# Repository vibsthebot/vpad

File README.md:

# vpad - a 50-key split keyboard

vpad is a wired, split, and ortholinear mechanical keyboard. both sides of the keyboard use the same board, and are connected using a ten wire cable. each half uses a 5x5 key matrix using choc v1 switches. 

## Features
well its just a simple keyboard, but its ortholinear, split, and choc!

## Firmware Overview
- Layer 0 - QWERTY (Default)
- Layer 1 - Numbers & Symbols
- Layer 2 - Function Keys

### Schematic

### PCB

### 3D Model

### BOM
| Qty	| Item	| Individual Price	| Total Price	|
| - | - | - | - |
| 1	|PCB + stencil	|$15.20	|$15.20	|
|50|	SOD123 Diode	| $0.02	| $1.15	| BAV21WTPMSCT-ND |
|1x80|	M3x4 heatset insert	|	$5.99	| https://www.amazon.com/Threaded-Inserts-Printing-Embedment-Automotive/dp/B0DJS5HWBY/ |
|50|	Choc v1|	$0.60	 |$30.00	|
|1x100|	M3x6 screws|$5.99	|https://www.amazon.com/Socket-Screws-Bolts-Thread-100pcs/dp/B07CMRQ3TB/|
|-|-|$58.33	|

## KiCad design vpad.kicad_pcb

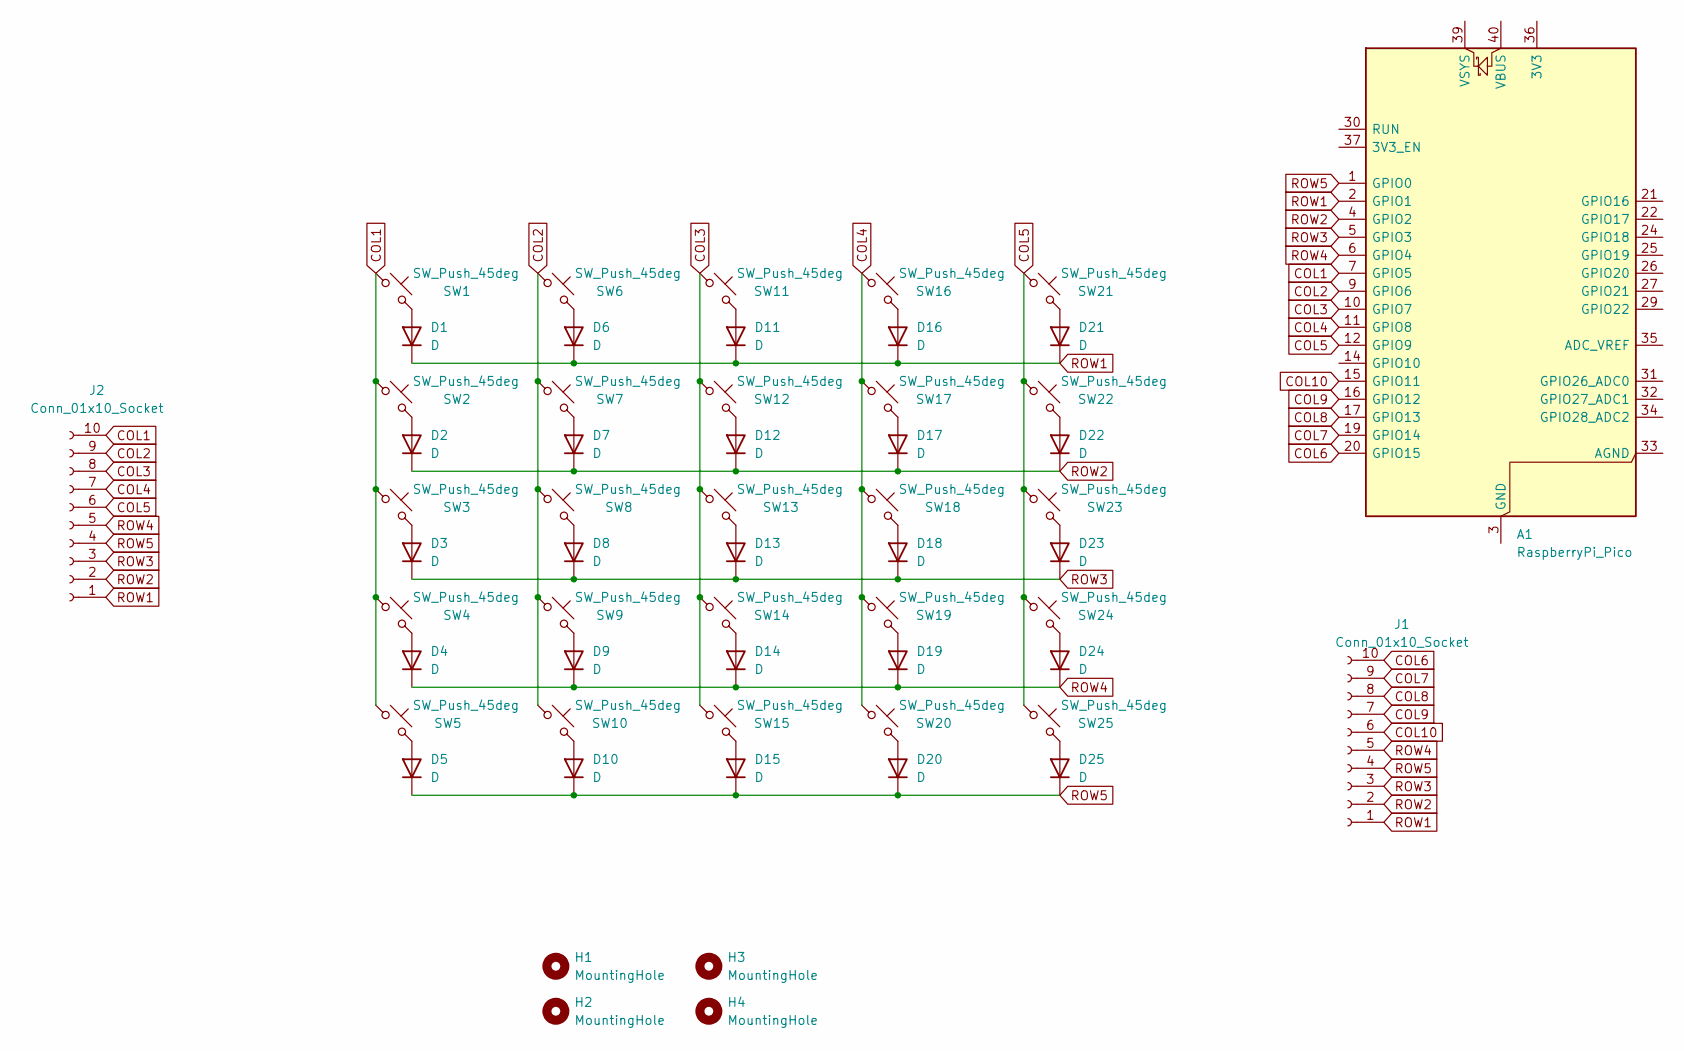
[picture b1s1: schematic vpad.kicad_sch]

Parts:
A1: RaspberryPi_Pico; RaspberryPi_Pico_Common_THT
D1, D2, D3, D4, D5, D6, D7, D8, D9, D10, D11, D12, D13, D14, D15, D16, D17, D18, D19, D20, D21, D22, D23, D24, D25: D; Diode_SOD-123
H1, H2, H3, H4: MountingHole; MountingHole_3.2mm_M3
J1, J2: Conn_01x10_Socket; PinSocket_1x10_P2.54mm_Vertical
SW1, SW2, SW3, SW4, SW5, SW6, SW7, SW8, SW9, SW10, SW11, SW12, SW13, SW14, SW15, SW16, SW17, SW18, SW19, SW20, SW21, SW22, SW23, SW24, SW25: SW_Push_45deg; Choc_V1_1.00u

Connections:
COL1: A1.7 (GPIO5), J2.10, SW1.1, SW2.1, SW3.1, SW4.1, SW5.1
COL2: A1.9 (GPIO6), J2.9, SW6.1, SW7.1, SW8.1, SW9.1, SW10.1
COL3: A1.10 (GPIO7), J2.8, SW11.1, SW12.1, SW13.1, SW14.1, SW15.1
COL4: A1.11 (GPIO8), J2.7, SW16.1, SW17.1, SW18.1, SW19.1, SW20.1
COL5: A1.12 (GPIO9), J2.6, SW21.1, SW22.1, SW23.1, SW24.1, SW25.1
COL6: A1.20 (GPIO15), J1.10
COL7: A1.19 (GPIO14), J1.9
COL8: A1.17 (GPIO13), J1.8
COL9: A1.16 (GPIO12), J1.7
COL10: A1.15 (GPIO11), J1.6
unnamed: A1.3 (GND), A1.8 (GND), A1.13 (GND), A1.18 (GND), A1.23 (GND), A1.28 (GND), A1.38 (GND)
unnamed: D1.2 (A), SW1.2
unnamed: D2.2 (A), SW2.2
unnamed: D3.2 (A), SW3.2
unnamed: D4.2 (A), SW4.2
unnamed: D5.2 (A), SW5.2
unnamed: D6.2 (A), SW6.2
unnamed: D7.2 (A), SW7.2
unnamed: D8.2 (A), SW8.2
unnamed: D9.2 (A), SW9.2
unnamed: D10.2 (A), SW10.2
unnamed: D11.2 (A), SW11.2
unnamed: D12.2 (A), SW12.2
unnamed: D13.2 (A), SW13.2
unnamed: D14.2 (A), SW14.2
unnamed: D15.2 (A), SW15.2
unnamed: D16.2 (A), SW16.2
unnamed: D17.2 (A), SW17.2
unnamed: D18.2 (A), SW18.2
unnamed: D19.2 (A), SW19.2
unnamed: D20.2 (A), SW20.2
unnamed: D21.2 (A), SW21.2
unnamed: D22.2 (A), SW22.2
unnamed: D23.2 (A), SW23.2
unnamed: D24.2 (A), SW24.2
unnamed: D25.2 (A), SW25.2
ROW1: A1.2 (GPIO1), D1.1 (K), D6.1 (K), D11.1 (K), D16.1 (K), D21.1 (K), J1.1, J2.1
ROW2: A1.4 (GPIO2), D2.1 (K), D7.1 (K), D12.1 (K), D17.1 (K), D22.1 (K), J1.2, J2.2
ROW3: A1.5 (GPIO3), D3.1 (K), D8.1 (K), D13.1 (K), D18.1 (K), D23.1 (K), J1.3, J2.3
ROW4: A1.6 (GPIO4), D4.1 (K), D9.1 (K), D14.1 (K), D19.1 (K), D24.1 (K), J1.5, J2.5
ROW5: A1.1 (GPIO0), D5.1 (K), D10.1 (K), D15.1 (K), D20.1 (K), D25.1 (K), J1.4, J2.4

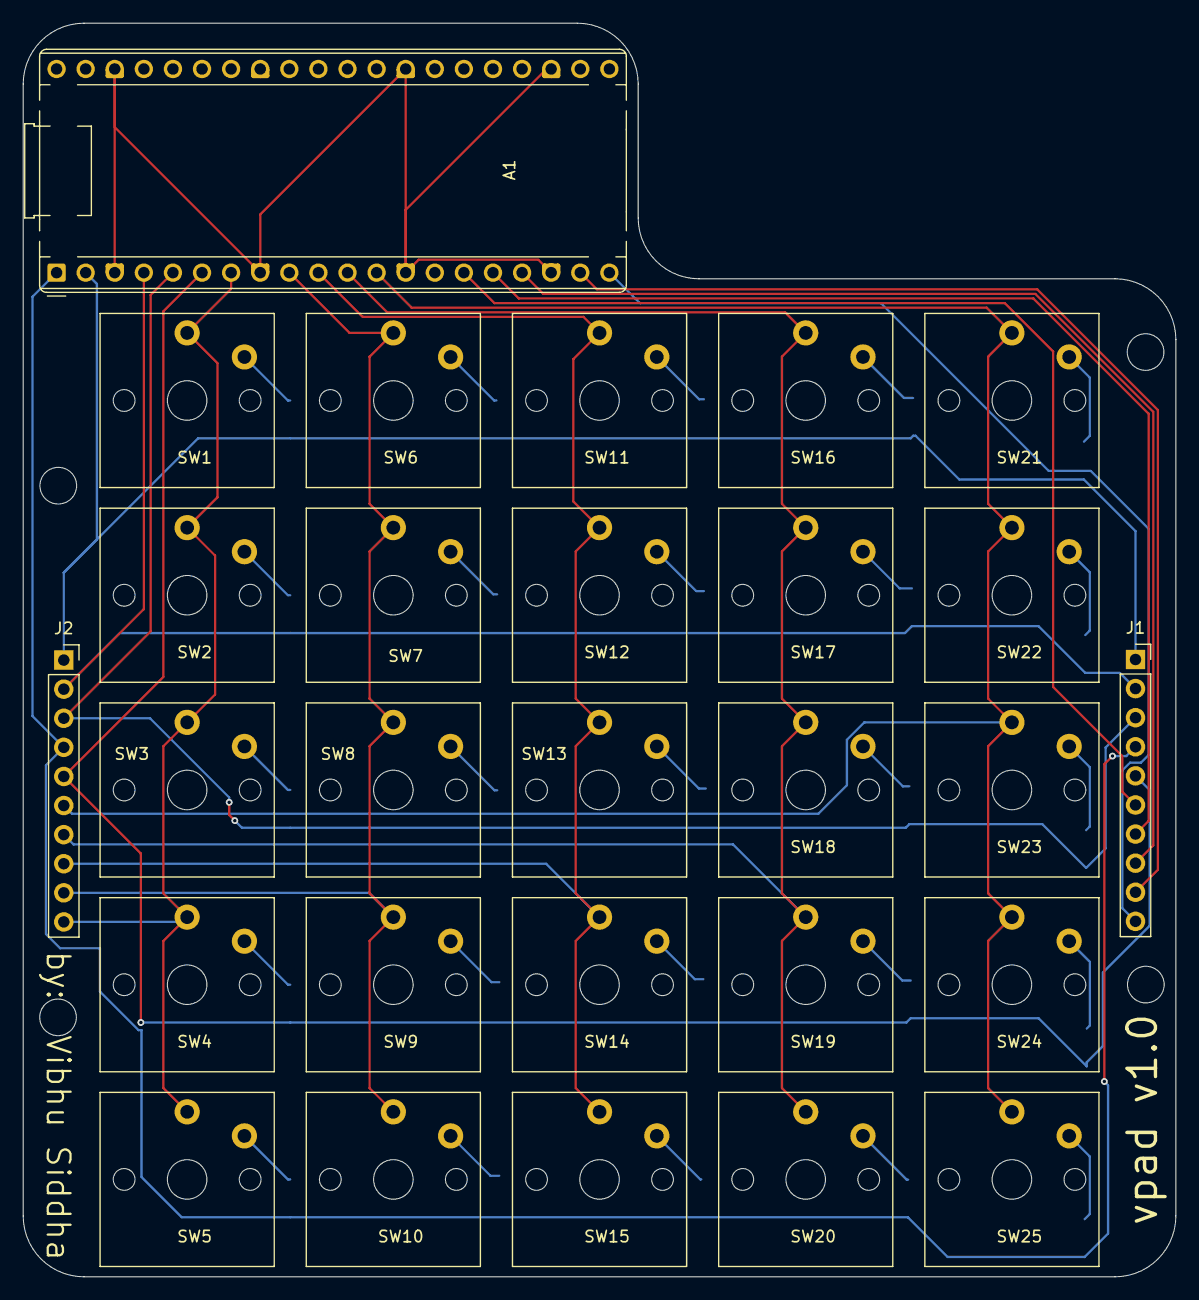
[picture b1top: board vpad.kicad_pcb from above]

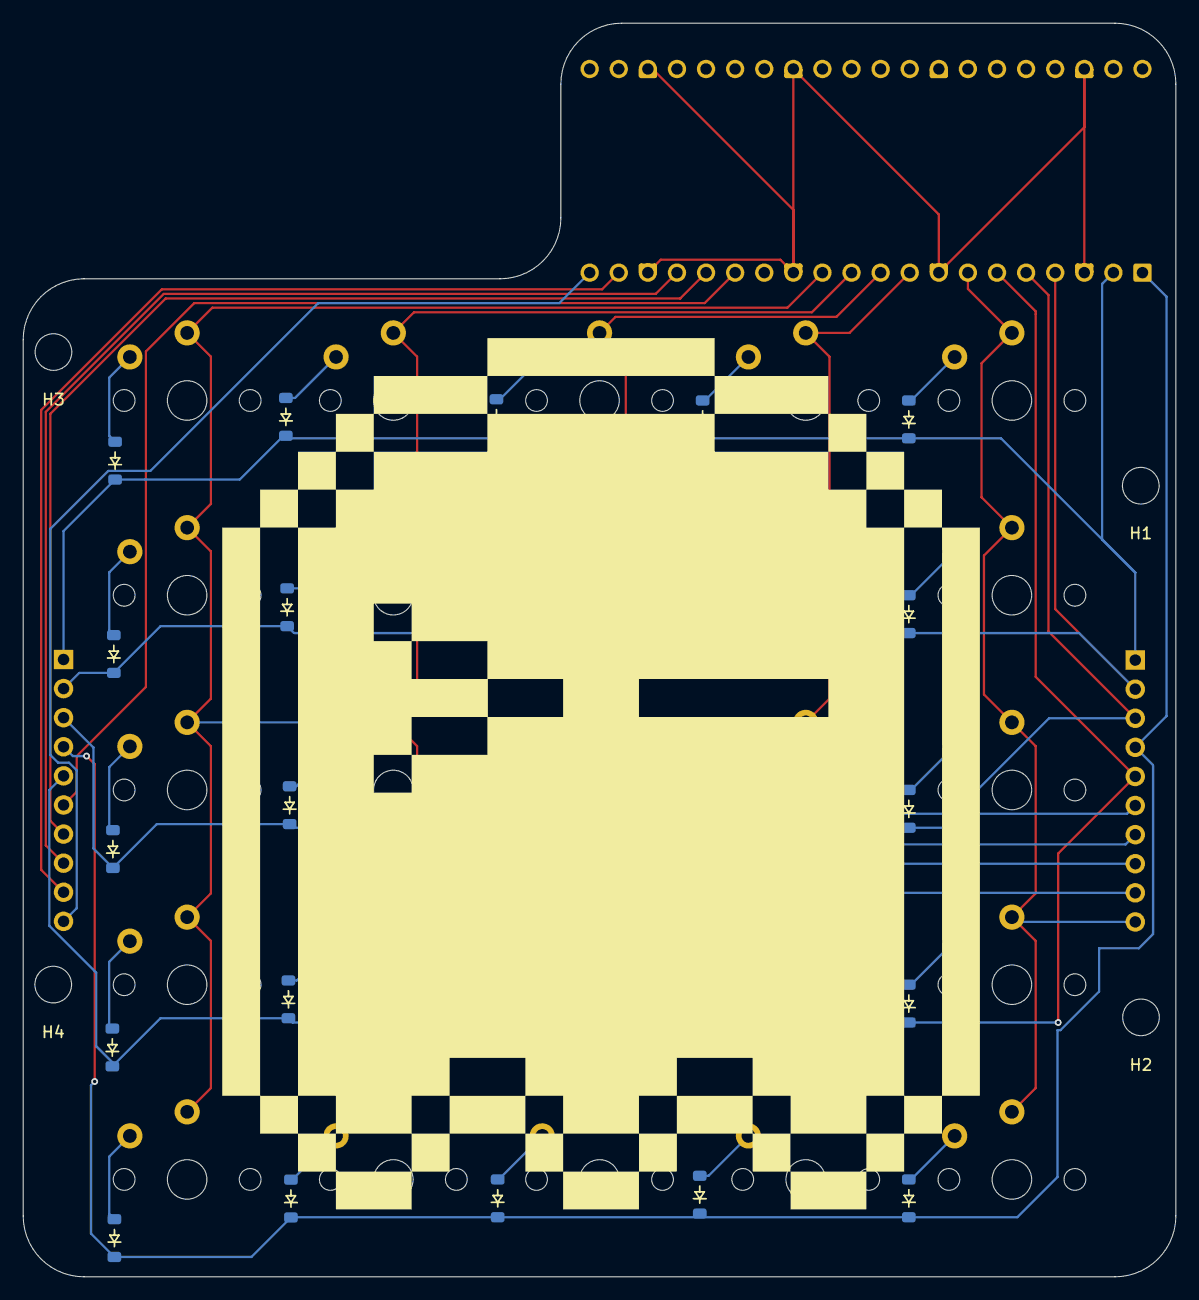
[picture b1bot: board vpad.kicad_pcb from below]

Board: 2 copper layers, 100.6 x 109.4 mm, 57 parts (29 on the bottom side), 41 nets.

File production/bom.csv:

Designator,Footprint,Quantity,Value,LCSC Part #
A1,RaspberryPi_Pico_Common_THT,1,RaspberryPi_Pico,
"D1, D10, D11, D12, D13, D14, D15, D16, D17, D18, D19, D2, D20, D21, D22, D23, D24, D25, D3, D4, D5, D6, D7, D8, D9",Diode_SOD-123,25,D,
"J1, J2",PinSocket_1x10_P2.54mm_Vertical,2,Conn_01x10_Socket,
"SW1, SW10, SW11, SW12, SW13, SW14, SW15, SW16, SW17, SW18, SW19, SW2, SW20, SW21, SW22, SW23, SW24, SW25, SW3, SW4, SW5, SW6, SW7, SW8, SW9",Choc_V1_1.00u,25,SW_Push_45deg,

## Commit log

2025-06-21 finished schematic and pcb!
2025-06-22 added mounting holes
2025-06-22 edited mounting to m3, added case
2025-06-22 Finished firmware
2025-06-22 Updated the journal
2025-06-23 finished bom and readme
2025-06-30 added bom to readme
